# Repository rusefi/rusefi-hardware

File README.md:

# rusefi-hardware

open source repo just for rusEFI Hardware

See also https://github.com/rusefi/rusefi/tree/master/hardware

# Breakouts

Many adapters are available assembled at https://shop.rusefi.com

## Connect into wires

Connector on one side, screw terminals or pads for your own harness on the other

* [24 pin](breakout-boards/Breakout-24pin) generic 24 pin to three connectors
* [135 pin](breakout-boards/Breakout-135-subaru-single) Subaru single connector (3D models only)
* [154 pin](breakout-boards/Breakout_154pin_284617-1-Connector) Volkswagen Audi VAG 284617-1

More "connect into wires" breakouts (35 to 134 pin: Mazda, Chrysler NGC, Mitsubishi, Motronic, Ford EEC-IV, VAG, BMW) live in the main repo at https://github.com/rusefi/rusefi/tree/master/hardware

## Superseal adapters

Vehicle-specific adapters keep the original harness intact: stock ECU connector on one side, superseal into a rusEFI ECU on the other

* [24 pin superseal](breakout-boards/Breakout-24pin-superseal) same as 24 pin but going into superseal
* [112 pin](breakout-boards/adapter-board-me17-112-B-schematic.pdf) Bosch ME17 ([rev A](breakout-boards/adapter-board-me17-112-A-schematic.pdf))
* [121 pin](breakout-boards/Ferrari-Maserati-121-adapter-rev-a.pdf) Ferrari/Maserati F136 engine
* [154 pin](breakout-boards/Breakout_154_kia_pb) Hyundai/Kia 1.6 GDI PB ([pinout](https://rusefi.com/docs/pinouts/hellen/hellen-hyundai-pb-mt/))
* [198 pin](breakout-boards/Breakout-198-Mustang) Ford Mustang Coyote ([pinout](https://rusefi.com/docs/pinouts/hellen/coyote/))
* [Mazda Miata NC](breakout-boards/Breakout-mazda-nc-0.1.pdf) ([pinout](https://rusefi.com/docs/pinouts/miata-nc/))
* [Mitsubishi Lancer Evo X](breakout-boards/mitsubishi-lancer-evo-x-rev-a.pdf)
* [Mitsubishi Mirage](breakout-boards/mitsubishi-mirage-adapter-0.3.pdf)
* [Subaru 2011](subaru-2011-adapter-docs) ([vehicle pinout](https://rusefi.com/docs/pinouts/subaru-2011/), [adapter pinout](https://rusefi.com/docs/pinouts/subaru%20adapter/))
* [154 pin](breakout-boards/Passat-2.0-MED9.1-adapter.pdf) Volkswagen Passat 2.0 MED9.1 GDI

## Other

* [ZF 8HP](ZF8HP%20Transmission) transmission installation board, solders in place of the stock TCU

Vehicle connector pinouts (no board, just `connectors/*.yaml` for [interactive pinouts](https://rusefi.com/docs/pinouts/)):

* [BMW N52](BMW-N52-146) 146 pin ([pinout](https://rusefi.com/docs/pinouts/BMW-N52-146/))
* [BMW N54](BMW-N54-146) 146 pin ([pinout](https://rusefi.com/docs/pinouts/BMW-N54-146/))
* [Honda OBD1](honda-obd1) 64 pin + 76 pin ([pinout](https://rusefi.com/docs/pinouts/uaefi/honda-obd1/))
* [Toyota JZA80](Toyota-JZA80) Supra MK4 E9/E10
* [Toyota JZA90](Toyota-JZA90) Supra MK5
* [Jatco](jatco) transmission
* [Kawasaki](kawasaki) motorcycle

# Modules

* [A4988](A4988_stepper_motor_driver) stepper motor driver
* [L9779WD](L9779WD-breakout) ASIC breakout
* [MC33810](MC33810-breakout) ASIC breakout
* [TLE9104](tle9104-breakout) ASIC breakout
* [LM1949](Low-Z_LM1949) low impedance injector driver
* [IR2302](IR2302-testboard) test board
* [VR-Hall](VR-Hall) VR/Hall conditioner
* [NCV1124](VR_ncv1124_test_module) VR test module
* [frequency divider](frequency-divider)
* [quad IGBT](quad-igbt) and [superseal IGBT](superseal-igbt) ignition drivers
* [stm32 Brain board 48pin](mini48-stm32)
* [uaBrain GM E38](uaBrain-gm-e38) hw-uaBrain module carrier for GM E38 (draft)
* [GDI-4ch](GDI-4ch), [GDI-6ch](GDI-6ch), [GDI-STM](GDI-STM) direct injection drivers
* [lambda-x2](lambda-x2), [wideband-F103](wideband-F103) wideband controllers
* [CDI-test](CDI-test), [stim](stim), [digital-inputs](digital-inputs) test and QC boards

# Classic designs

Frankenso, Frankenstein and other legacy designs are in [classic-designs](classic-designs)

# Important note

Depends on libraries from https://github.com/rusefi/kicad-libraries

If you git clone be sure to also

`git submodule update --init`

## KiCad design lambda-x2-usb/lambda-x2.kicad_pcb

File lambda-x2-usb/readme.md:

# About

🟢 rev1 is known to work 🟢

pinout source https://github.com/rusefi/rusefi/tree/master/firmware/config/boards/lambda-x2

https://www.shop.rusefi.com/shop/p/dual-channel-wbo

Features:
* STM32F103 dual channel wideband AFR controller supporting Bosch LSU4.9 and LSU4.2 (LSU_ADV work in progress)
* CAN and analog output
* Bluetooth or USRT TunerStudio connectivity

Options (not icluded in default BOM)
* x2 EGT input using MAX31855KASA or MAX31856
* x2 auxilary analog input: 0..5V with pull-up or pull-down (configurable by soldering resistor). One can be used to source 5V to external sensor.
* x2 2 auxilary output 0..5V. Also can be used for slow PWM signal output.
* x2 open drain outputs

In development:
* MegaSquirt compatible pass-through connection over CAN http://www.msgpio.com/manuals/mshift/cpt.html (in progress)

See [interactive pinout](https://rusefi.com/docs/pinouts/lambda-x2/)

See [wire colors](https://github.com/rusefi/rusefi/wiki/WBO#naming-convention) for standart LSU wire collors and connectors pinouts.

Current stable [FW release](https://github.com/dron0gus/wideband/releases/tag/release_zero) use "dual-rev1" files

Firmware [sources](https://github.com/dron0gus/wideband) (based on https://github.com/mck1117/wideband).

See rusEFI forum: [F103 dual channel wideband controller + EGT + 2 x AUX In + 2 Aux out](https://rusefi.com/forum/viewtopic.php?f=4&t=2314)

See also https://github.com/rusefi/rusefi/wiki/WBO

# Known issues

## DFU mode/floating PB2

BOOT0 = 1, BOOT1 = 0 pattern is used to enter DFU bootloader on power/reset. BOOT0 is controled by jumper/button. BOOT1 (PB2) is used as bias current source for LSU4.9 and floating.

Use jumper wire to connect PB2 (through bias resistor) to GND: connect A2 pin of main connector with GND (J4 AUX connector pin 10)

## ESR measurement crosstalk between channels (rev0 and rev1)

HW has three different outputs for Nernst cell ESR measurement with different output resistance: 6.8K for LSU4.2, 22K for LSU4.9 and 47K for LSUADV. Idea was to allow the user to set the type of sensor from SW only.

Each ESR output is driven by one MCU GPIO. GPIOs for unused ESR measurement outputs are kept in Hi-Z (input) state and does not affect ESR measurement.

Same GPIO drivers ESR outputs for both channels. **This is the root cause of problem**

Problem: unused ESR output with GPIO in Hi-Z state connect Nernst cell outputs from left and right channel through two resistors. This causes crosstalk between channels and inaccurate ESR measurement. Wrong ESR measurement causes incorrect sensor temperature calculation. This can lead to inaccurate AFR measurement, overheating or underheating of the sensor.

Same issue for LSU4.9 bias resistors R22 and R70.

Solution:

Boards come with all ESR drive resistors populated. You have to remove unnecessary resistors.

If LSU4.2 sensor is used: remove R24, R25, R71, R72, R22, R70. Keep R41 and R73 - 6.8K

If LSU4.9 sensor is used: remove R25, R41, R72, R73. Keep R24 and R71 - 22K

If LSUADV sensor is used: remove R24, R41, R71, R73, R22, R70. Keep R25 and R72 - 47K

This will be (or not) solved in next revision of HW.

# Pinout

## Connectors pinout

[Main connector interactive Pinout](https://rusefi.com/docs/pinouts/lambda-x2/)

J4 is AUX connector available on PCB. SPI and I2C interfaces along with 3.3V and 5V are routed to this connector. Can be used to connect some small disply (SW not implemented yet)

J3 connector is for flashing and powering board on table. Also can be used for TunerStudion connection.

J1 and J2 are JTAG connectos.

## Uart pinout

J3 connector. Colors are default for cheap usb-to-uart converters based on CP2101 or FTDI232
Connect red wire if you want to power device from USB.
Default baud rate is 115200.

# Bluetooth

No extra steps needed to initialize JDY-33. Default device name is "RusEFI WBO x2" (or "RuseEFI WBO x2 BLE" for BT BLE)

Default baud rate is 115200.

# TunerStudio configuration

Baudrate is 115200
[.ini file](https://github.com/dron0gus/wideband/blob/master/firmware/ini/rusefi_wb_f1_dual.ini) for both UART and BT connection.

Both interfaces can be used simultaneously for data logging but not for settings change (from rev1).

Rev0 share same UART for both interfaces.

# Firmware Upload

Two ways to program using STM32CubeProgrammer

* recommended way: using UART connectivity. Power device up while shorting BOOT0 jumper to enter DFU mode (see "DFU mode/floating PB2" issue above)
* st-link if you have tc2030 spring-loaded cable.
* update over CAN or UART (J3) using OpenBLT (update over BT is in progress)

TL,DR: 9600 nothing connected on main connector

## Updating over UART using DFU mode

1. Disconnect main connector. If you are going to apply +12V power through main connector - make sure that nothing else is connected to WBO (LSU sensors, any load, etc). But I recommend flash using +5V from USB.
   
2. connect USB to uart connector to J3 connector: gnd, rx and tx.
Don't forget to cross Rx-`Tx (adapter's Tx goes to WBO's Rx, WBO's Tx goes to adapter's Rx).
If you going to power WBO from USB port - also attach 5V line. Do not connect +5 from USB adapter if you are going to use +12V supply through main connector.

### Linux way

3. Install stm32flash utility

`apt-get install stm32flash`

4. Press and hold BOOT0 button on the bottom of PCB. Or short BOOT0 PCB jumper if button is not populated on your board.

5. Apply power (while still holding BOOT0 button) to board

6. Run

`stm32flash /dev/ttyUSB0 -w wideband.hex`

### Windows way

3. Download and install STM32 Flash Loader Demonstrator. (Alternative tool is stm32flash - not covered in this instruction)

4. Figure out USB to serial serial port number: 

5. Start Flash Loader Demonstrator GUI application, select correct COM port. Optional: reduce timeout to 1 second:

6. Press and hold BOOT0 button on the bottom of PCB. Or short BOOT0 PCB jumper if button is not populated on your board.

7. Apply power (while holding BOOT0 button) to board and press Next in application. After app detects chip you should see something similar to:

8. Press next, select "Download to device", select wideband.bin file. Select "Jump to user application" and "Verify after download"

9. Press Next and wait for flash/verification ends.

## Updating using JTAG

DBD.

## Update using OpenBLT

OpenBLT https://www.feaser.com/openblt/doku.php

1. Restart device to OpenBLT mode using "Reset to OpenBLT" button under Controller -> ECU tools in TunerStudio.
   
2. Close TunerStudio to release serial port

3. Open BootCommander, select correct serial port, select wideband_update.srec file.

# Changelog

## rev 1
* Switch to 64 pin STM32/GD32
* Add 8MHz HSE oscillator (better clock stability for CAN over wide temperature range)
* Use DAC (instead of PWM) outputs for driving Ip
* Move BT to UART3/USART3, keep USART1 for bootloader/debug
* Drive BT's EN signal from MCU
* Fix RC filters on heater outputs for better voltage measurement
* Use separate ADC input for Vbat measurement
* Use ADC channels for AUX outputs monitoring/diagnostic
* Use PWM noise cancelation circuit on AUX analog outputs
* Removed useless/non-functional protection of Vm outputs
* Fix board outline to fit two types of enclosure ("plastic top" and "alloy brick")
* Add testpoints for TC2030 JTAG probe
* Add buttons for Reset and Boot0
* Add Cfg1 and jumpers
* Replace fuse holder with resettable 0.2A 33V fuse
* Two status LEDs for separate status indication for left and right channel
* Silkscreen labels around testpoints
* Silkscreen labels at uart connector on both sides of PCB
* Un_3x_sense formula is now 0.247 + 3.15 * (Un - Vm)
* Un_sense (not gained) is also routed to ADC input
* Protection from possible Ip current when MCU in reset/bootloader
* White "power on" LED replaced with green
* Main connector pinout added to top silkscreen
* AUX connector pinout added to top silkscreen

## rev 0

Seems to work with proper C10/C35 using https://github.com/rusefi/wideband/releases/tag/20230210-does-not-match-binaris

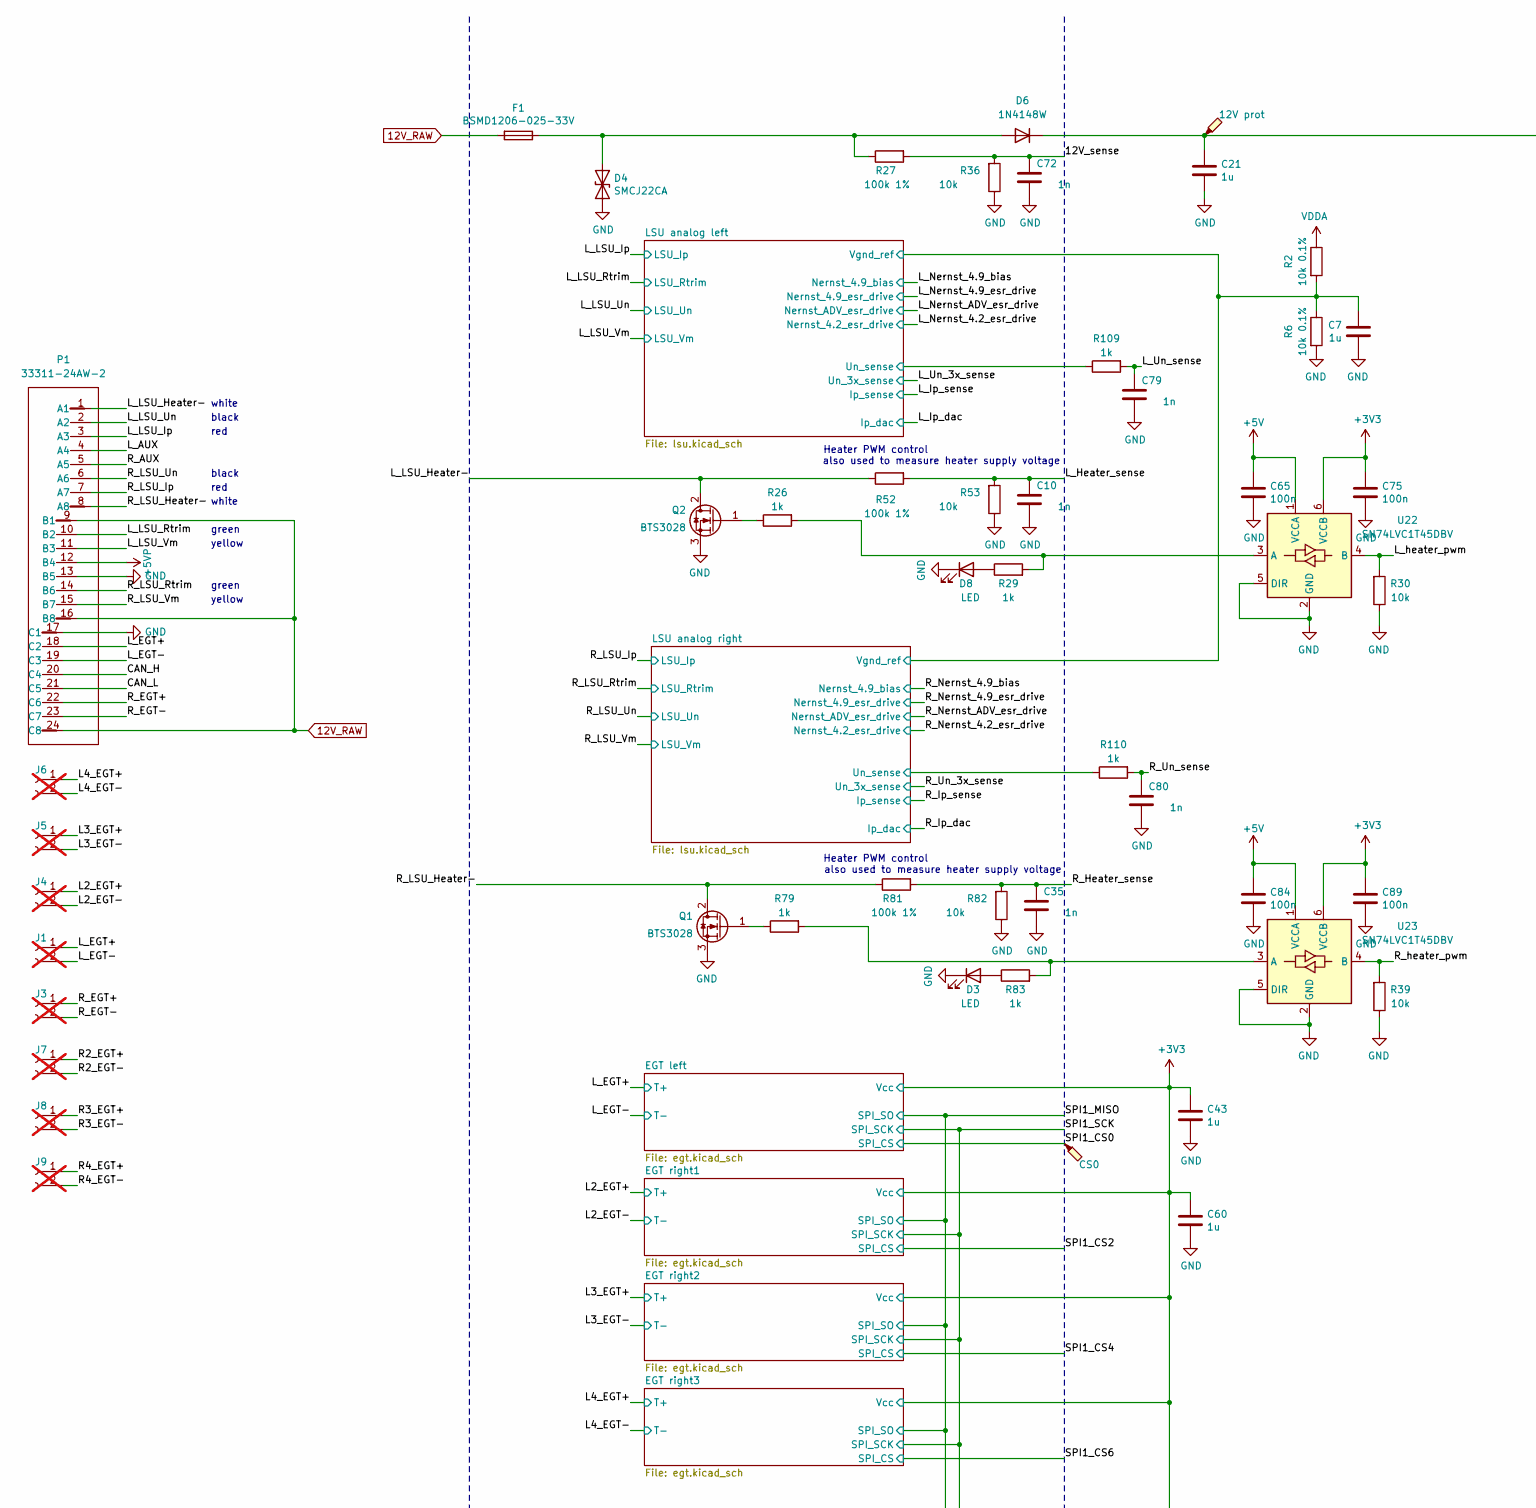
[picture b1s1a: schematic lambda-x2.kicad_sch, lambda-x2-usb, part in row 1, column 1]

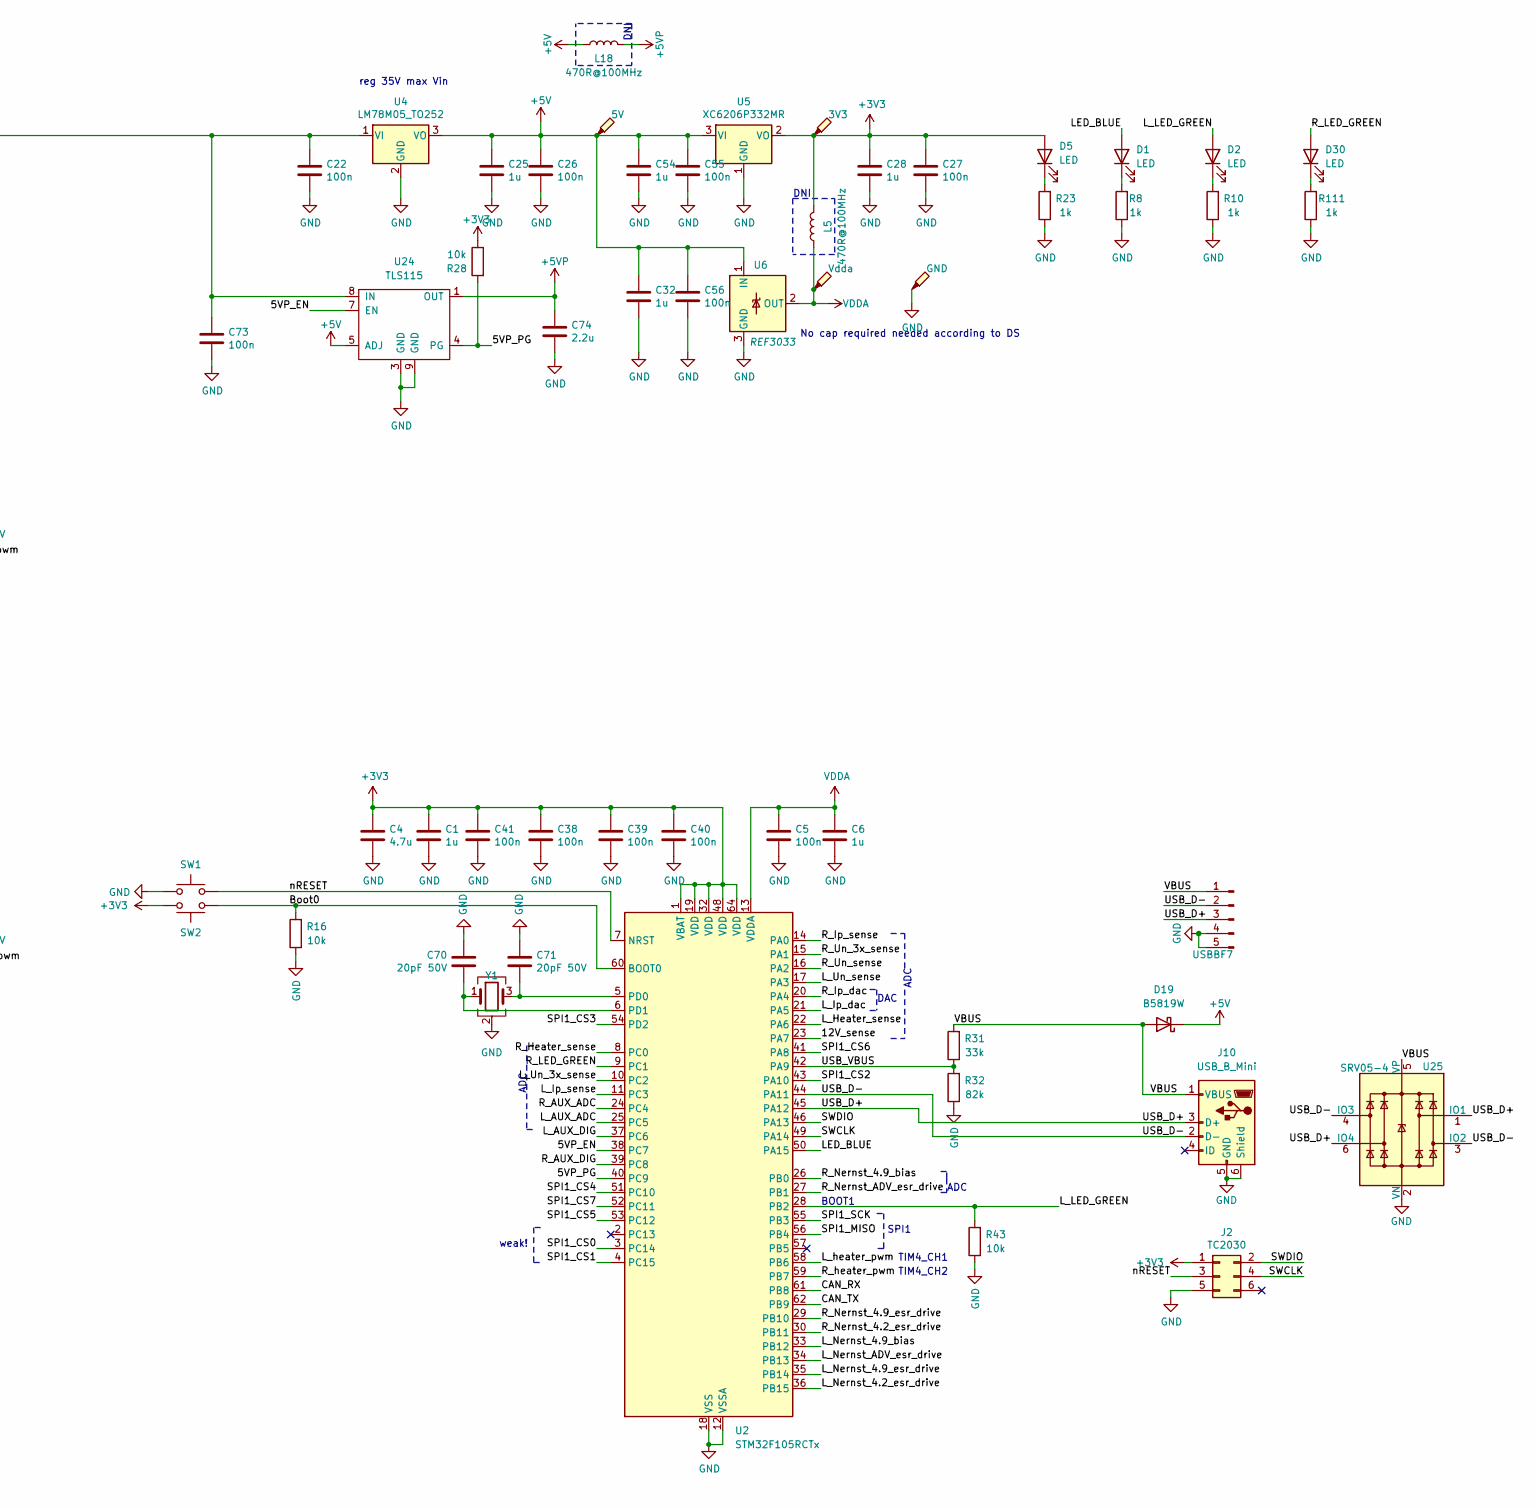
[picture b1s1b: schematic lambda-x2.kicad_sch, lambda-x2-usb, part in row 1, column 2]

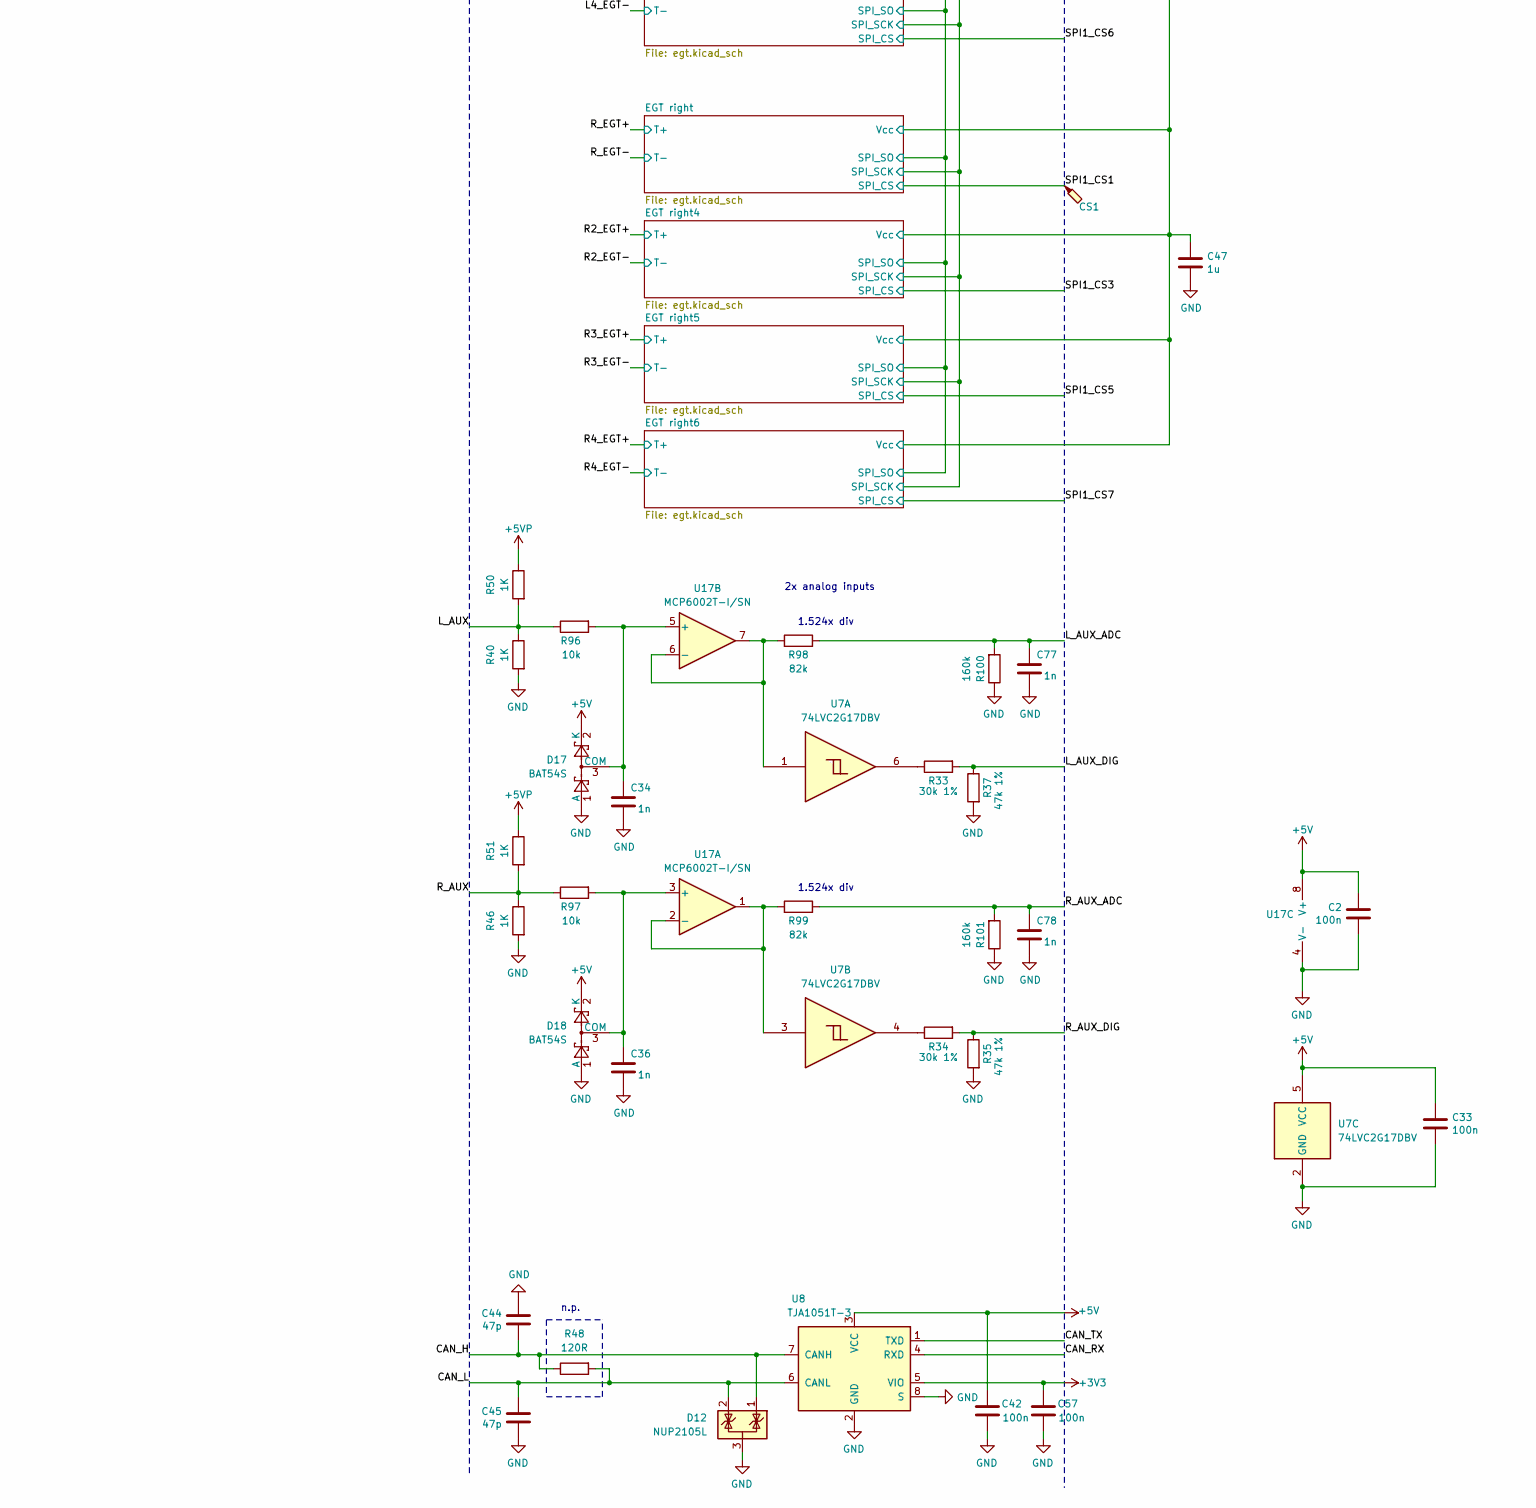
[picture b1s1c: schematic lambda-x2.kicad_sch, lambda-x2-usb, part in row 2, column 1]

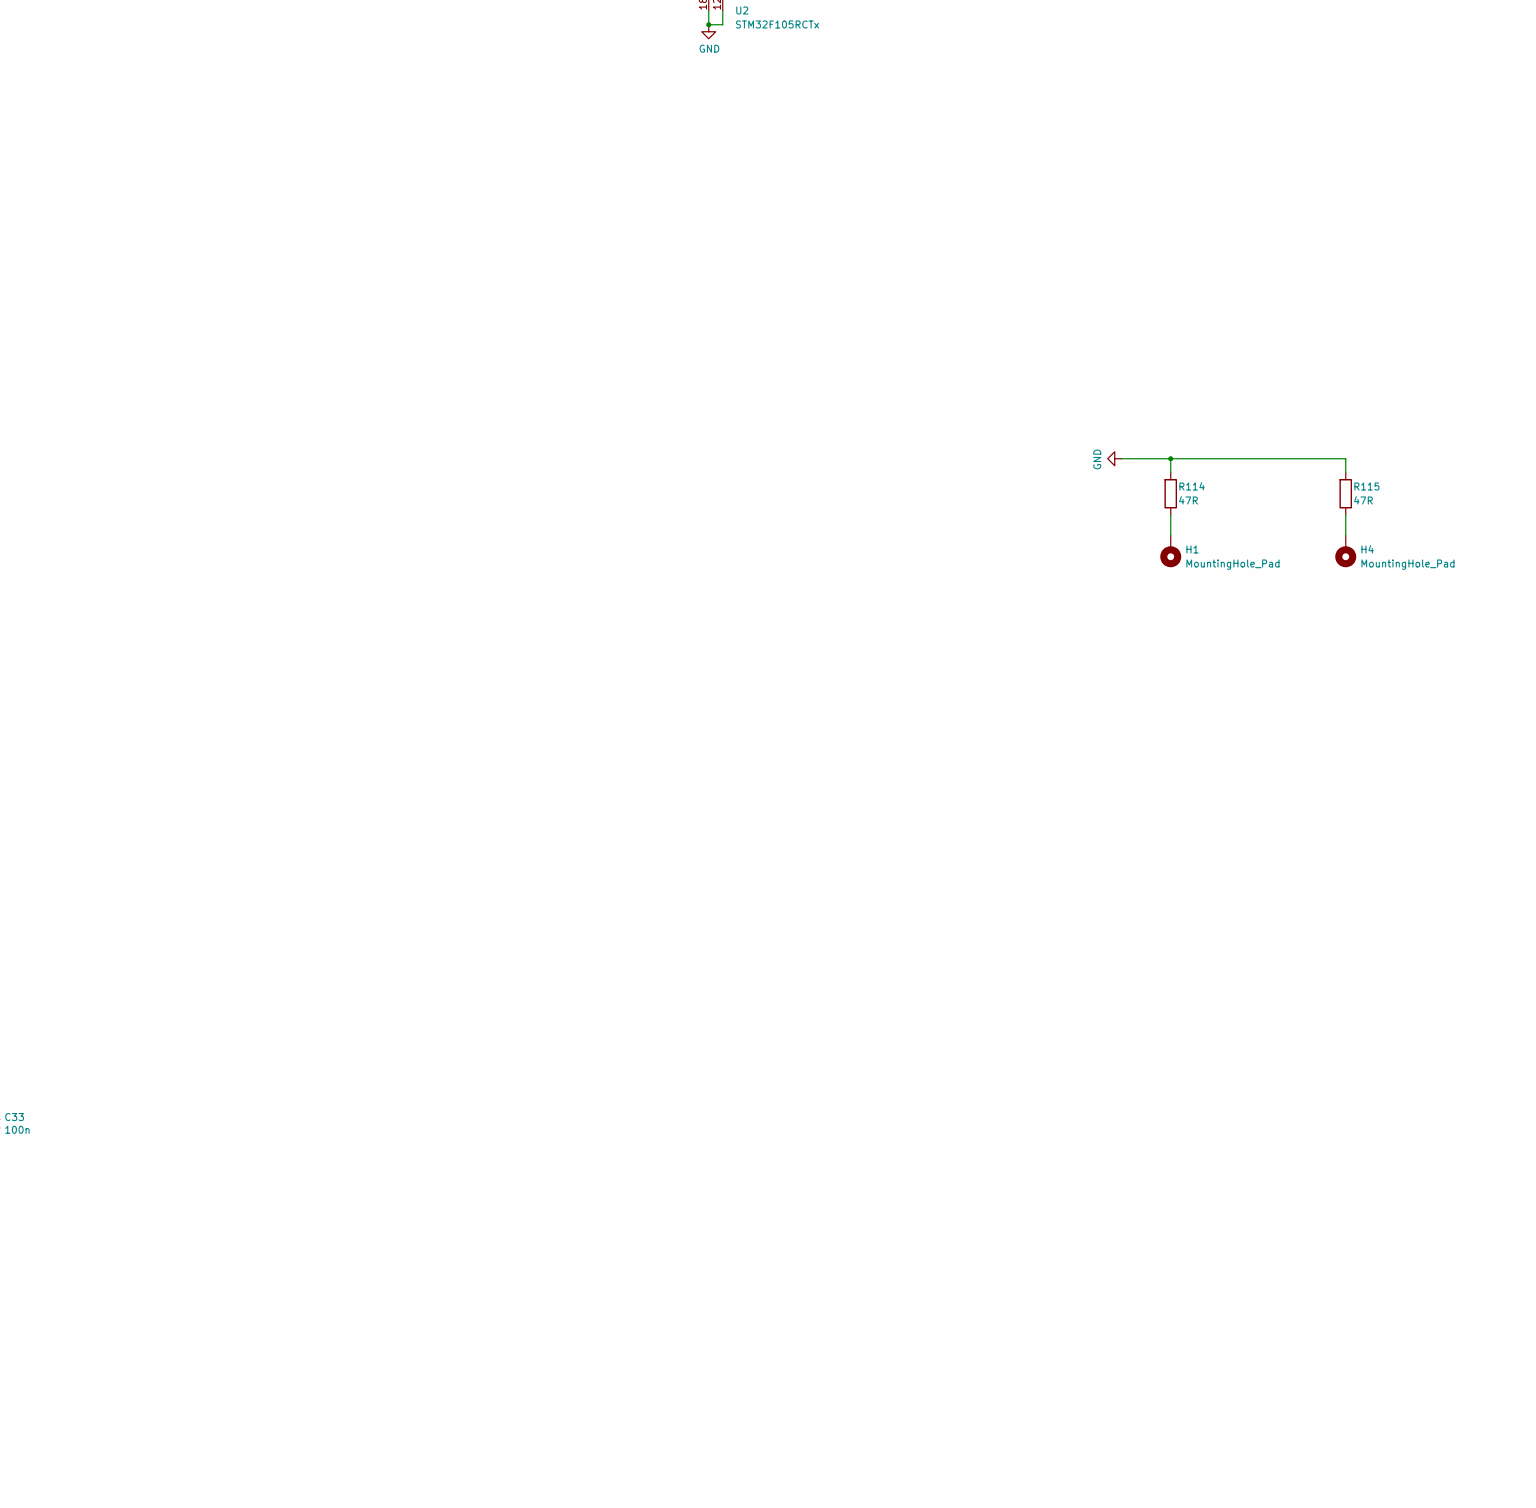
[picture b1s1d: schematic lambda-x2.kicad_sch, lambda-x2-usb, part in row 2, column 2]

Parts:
C1, C6, C7, C25, C28, C32, C43, C47, C54, C60: 1u; C_0402_1005Metric; LCSC C52923
C2, C5, C26, C27, C33, C38, C39, C40, C41, C42, C55, C56, C57, C65, C75, C84, C89: 100n; C_0402_1005Metric; LCSC C1525
C4: 4.7u; C_0402_1005Metric; LCSC C23733
C10, C34, C35, C36, C72, C77, C78, C79, C80: 1n; C_0402_1005Metric; LCSC C106205
C21: 1u; C_0603_1608Metric; LCSC C15849
C22, C73: 100n; C_0603_1608Metric; LCSC C14663
C44, C45: 47p; C_0402_1005Metric; LCSC C1567
C70, C71: 20pF 50V; C_0402_1005Metric; LCSC C107000
C74: 2.2u; C_0603_1608Metric; LCSC C23630
D1: LED; LED_0603_1608Metric; LCSC C497940
D2, D5, D30: LED; LED_0603_1608Metric; LCSC C965804
D3, D8: LED; LED_0603_1608Metric; LCSC C2286
D4: SMCJ22CA; D_SMC; LCSC C310038
D6: 1N4148W; D_SOD-123; LCSC C81598
D12: NUP2105L; SOT-23; LCSC C284104
D17, D18: BAT54S; SOT-23; LCSC C47546
D19: B5819W; D_SOD-123; LCSC C8598
F1: BSMD1206-025-33V; Fuse_1206_3216Metric; LCSC C2977524
H1, H4: MountingHole_Pad; MountingHole_2.5mm_Pad_Via
J1, J3, J4, J5, J7, J8, J9: Conn_01x02_Socket; PCC-SMP-V-one-leg; not fitted
J2: TC2030; Tag-Connect_TC2030-IDC-NL_2x03_P1.27mm_Vertical
J6: Conn_01x02_Socket; PCC-SMP-V; not fitted
J10: USB_B_Mini; USB-MINI-B-VERTICAL; LCSC C13453
J11: USBBF7; LCSC C17899327
L5, L18: 470R@100MHz; L_0603_1608Metric; LCSC C97853
P1: 33311-24AW-2; LCSC C5349068
Q1, Q2: BTS3028; TO-252-2; LCSC C112639
R2, R6: 10k 0.1%; R_0603_1608Metric; LCSC C309083
R8, R10, R23, R26, R29, R79, R83, R109, R110, R111: 1k; R_0402_1005Metric; LCSC C11702
R16, R28, R30, R36, R39, R43, R53, R82, R96, R97: 10k; R_0402_1005Metric; LCSC C25744
R27, R52, R81: 100k 1%; R_0603_1608Metric; LCSC C25803
R31: 33k; R_0402_1005Metric; LCSC C25779
R32: 82k; R_0402_1005Metric; LCSC C4142
R33, R34: 30k 1%; R_0603_1608Metric; LCSC C22984
R35, R37: 47k 1%; R_0603_1608Metric; LCSC C25819
R40, R46, R50, R51: 1K; R_0603_1608Metric; LCSC C21190
R48: 120R; R_1206_3216Metric; LCSC C176250
R98, R99: 82k; R_0402_1005Metric; LCSC C325373
R100, R101: 160k; R_0402_1005Metric; LCSC C409854
R114, R115: 47R; R_0603_1608Metric; LCSC C328363
SW1, SW2: SW_SPST_CK_RS282G05A3; LCSC C398054
TP7: 5V; TestPoint_Pad_D1.0mm
TP8: 3V3; TestPoint_Pad_D1.0mm
TP9: Vdda; TestPoint_Pad_D1.0mm
TP24: GND; TestPoint_Pad_D1.0mm
TP25: CS0; TestPoint_Pad_D1.0mm
TP26: CS1; TestPoint_Pad_D1.0mm
TP27: 12V prot; TestPoint_Pad_D1.0mm
U2: STM32F105RCTx; LQFP-64_10x10mm_P0.5mm; LCSC C8345
U4: LM78M05_TO252; TO-252-2; LCSC C58069
U5: XC6206P332MR; SOT-23-3; LCSC C5446
U6: REF3033; SOT-23; LCSC C36658
U7: 74LVC2G17DBV; SOT-23-6; LCSC C10429
U8: TJA1051T-3; SOIC-8_3.9x4.9mm_P1.27mm; LCSC C38695
U17: MCP6002T-I/SN; SOIC-8_3.9x4.9mm_P1.27mm; LCSC C7377
U22, U23: SN74LVC1T45DBV; SOT-23-6; LCSC C7843
U24: TLS115; PG-DSO-8-43; LCSC C3747428
U25: SRV05-4; SOT-23-6; LCSC C6454456
Y1: XXDCELNANF-8MHZ; Crystal_SMD_3225-4Pin_3.2x2.5mm; LCSC C367183

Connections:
12V_RAW: F1.2, P1.9 (B1), P1.16 (B8), P1.24 (C8)
+3V3: C1.1, C4.1, C27.1, C28.1, C38.1, C39.1, C40.1, C41.1, C43.1, C47.1, C57.1, C60.1, C75.1, C89.1, D5.2 (A), J2.1, L5.2, R28.1, SW2.2, TP8.1 (1_1), U2.1 (VBAT), U2.19 (VDD), U2.32 (VDD), U2.48 (VDD), U2.64 (VDD), U5.2 (VO), U8.5 (VIO), U22.6 (VCCB), U23.6 (VCCB); also elsewhere on the board
+5V: C2.1, C25.1, C26.1, C32.1, C33.1, C42.1, C54.1, C55.1, C56.1, C65.1, C84.1, D17.2 (K), D18.2 (K), D19.1 (K), L18.1, TP7.1 (1_1), U4.3 (VO), U5.3 (VI), U6.1 (IN), U7.5 (VCC), U8.3 (VCC), U17.8 (V+), U22.1 (VCCA), U23.1 (VCCA), U24.5 (ADJ)
+5VP: C74.1, L18.2, P1.12 (B4), R50.1, R51.1, U24.1 (OUT)
/5VP_EN: U2.38 (PC7), U24.7 (EN)
/5VP_PG: R28.2, U2.40 (PC9), U24.4 (PG)
/12V_sense: C72.1, R27.2, R36.2, U2.23 (PA7)
/Boot0: R16.2, SW2.1, U2.60 (BOOT0)
/CAN_H: C44.2, D12.1 (K), P1.20 (C4), R48.1, U8.7 (CANH)
/CAN_L: C45.1, D12.2 (K), P1.21 (C5), R48.2, U8.6 (CANL)
/CAN_RX: U2.61 (PB8), U8.4 (RXD)
/CAN_TX: U2.62 (PB9), U8.1 (TXD)
/L2_EGT+: J4.1; also elsewhere on the board
/L2_EGT-: J4.2; also elsewhere on the board
/L3_EGT+: J5.1; also elsewhere on the board
/L3_EGT-: J5.2; also elsewhere on the board
/L4_EGT+: J6.1; also elsewhere on the board
/L4_EGT-: J6.2; also elsewhere on the board
/LED_BLUE: D1.2 (A), U2.50 (PA15)
/LSU analog left/Un_sense: R109.1; also elsewhere on the board
/LSU analog left/Vgnd_ref: C7.1, R2.2, R6.1; also elsewhere on the board
/LSU analog right/Un_sense: R110.1; also elsewhere on the board
/L_AUX: P1.4 (A4), R40.1, R50.2, R96.1
/L_AUX_ADC: C77.1, R98.1, R100.2, U2.25 (PC5)
/L_AUX_DIG: R33.2, R37.1, U2.37 (PC6)
/L_EGT+: J1.1, P1.18 (C2); also elsewhere on the board
/L_EGT-: J1.2, P1.19 (C3); also elsewhere on the board
/L_Heater_sense: C10.1, R52.2, R53.2, U2.22 (PA6)
/L_Ip_dac: U2.21 (PA5); also elsewhere on the board
/L_Ip_sense: U2.11 (PC3); also elsewhere on the board
/L_LED_GREEN: D2.2 (A), R43.2, U2.28 (PB2)
/L_LSU_Heater-: P1.1 (A1), Q2.2 (D), R52.1
/L_LSU_Ip: P1.3 (A3); also elsewhere on the board
/L_LSU_Rtrim: P1.10 (B2); also elsewhere on the board
/L_LSU_Un: P1.2 (A2); also elsewhere on the board
/L_LSU_Vm: P1.11 (B3); also elsewhere on the board
/L_Nernst_4.2_esr_drive: U2.36 (PB15); also elsewhere on the board
/L_Nernst_4.9_bias: U2.33 (PB12); also elsewhere on the board
/L_Nernst_4.9_esr_drive: U2.35 (PB14); also elsewhere on the board
/L_Nernst_ADV_esr_drive: U2.34 (PB13); also elsewhere on the board
/L_Un_3x_sense: U2.10 (PC2); also elsewhere on the board
/L_Un_sense: C79.1, R109.2, U2.17 (PA3)
/L_heater_pwm: R30.2, U2.58 (PB6), U22.4 (B)
/R2_EGT+: J7.1; also elsewhere on the board
/R2_EGT-: J7.2; also elsewhere on the board
/R3_EGT+: J8.1; also elsewhere on the board
/R3_EGT-: J8.2; also elsewhere on the board
/R4_EGT+: J9.1; also elsewhere on the board
/R4_EGT-: J9.2; also elsewhere on the board
/R_AUX: P1.5 (A5), R46.1, R51.2, R97.1
/R_AUX_ADC: C78.1, R99.1, R101.2, U2.24 (PC4)
/R_AUX_DIG: R34.2, R35.1, U2.39 (PC8)
/R_EGT+: J3.1, P1.22 (C6); also elsewhere on the board
/R_EGT-: J3.2, P1.23 (C7); also elsewhere on the board
/R_Heater_sense: C35.1, R81.2, R82.2, U2.8 (PC0)
/R_Ip_dac: U2.20 (PA4); also elsewhere on the board
/R_Ip_sense: U2.14 (PA0); also elsewhere on the board
/R_LED_GREEN: D30.2 (A), U2.9 (PC1)
/R_LSU_Heater-: P1.8 (A8), Q1.2 (D), R81.1
/R_LSU_Ip: P1.7 (A7); also elsewhere on the board
/R_LSU_Rtrim: P1.14 (B6); also elsewhere on the board
/R_LSU_Un: P1.6 (A6); also elsewhere on the board
/R_LSU_Vm: P1.15 (B7); also elsewhere on the board
/R_Nernst_4.2_esr_drive: U2.30 (PB11); also elsewhere on the board
/R_Nernst_4.9_bias: U2.26 (PB0); also elsewhere on the board
/R_Nernst_4.9_esr_drive: U2.29 (PB10); also elsewhere on the board
/R_Nernst_ADV_esr_drive: U2.27 (PB1); also elsewhere on the board
/R_Un_3x_sense: U2.15 (PA1); also elsewhere on the board
/R_Un_sense: C80.1, R110.2, U2.16 (PA2)
/R_heater_pwm: R39.2, U2.59 (PB7), U23.4 (B)
/SPI1_CS0: TP25.1 (1_1), U2.3 (PC14); also elsewhere on the board
/SPI1_CS1: TP26.1 (1_1), U2.4 (PC15); also elsewhere on the board
/SPI1_CS2: U2.43 (PA10); also elsewhere on the board
/SPI1_CS3: U2.54 (PD2); also elsewhere on the board
/SPI1_CS4: U2.51 (PC10); also elsewhere on the board
/SPI1_CS5: U2.53 (PC12); also elsewhere on the board
/SPI1_CS6: U2.41 (PA8); also elsewhere on the board
/SPI1_CS7: U2.52 (PC11); also elsewhere on the board
/SPI1_MISO: U2.56 (PB4); also elsewhere on the board
/SPI1_SCK: U2.55 (PB3); also elsewhere on the board
/SWCLK: J2.4, U2.49 (PA14)
/SWDIO: J2.2, U2.46 (PA13)
/USB_D+: J10.3 (D+), J11.3, U2.45 (PA12), U25.1 (IO1), U25.6 (IO4)
/USB_D-: J10.2 (D-), J11.2, U2.44 (PA11), U25.3 (IO2), U25.4 (IO3)
/USB_VBUS: R31.1, R32.2, U2.42 (PA9)
/VBUS: D19.2 (A), J10.1 (VBUS), J11.1, R31.2, U25.5 (VP)
/nRESET: J2.3, SW1.2, U2.7 (NRST)
GND: C1.2, C2.2, C4.2, C5.2, C6.2, C7.2, C10.2, C21.2, C22.2, C25.2, C26.2, C27.2, C28.2, C32.2, C33.2, C34.2, C35.2, C36.2, C38.2, C39.2, C40.2, C41.2, C42.2, C43.2, C44.1, C45.2, C47.2, C54.2, C55.2, C56.2, C57.2, C60.2, C65.2, C70.1, C71.1, C72.2, C73.2, C74.2, C75.2, C77.2, C78.2, C79.2, C80.2, C84.2, C89.2, D3.1 (K), D4.2 (A2), D8.1 (K), D12.3 (A), D17.1 (A), D18.1 (A), J2.5, J10.5 (GND), J10.6 (Shield), J11.4, J11.5, P1.13 (B5), P1.17 (C1), Q1.3 (S), Q2.3 (S), R6.2, R8.1, R10.1, R16.1, R23.1, R30.1, R32.1, R35.2, R36.1, R37.2, R39.1, R40.2, R43.1, R46.2, R53.1, R82.1, R100.1, R101.1, R111.1, R114.2, R115.2, SW1.1, TP24.1 (1_1), U2.12 (VSSA), U2.18 (VSS), U2.31 (VSS), U2.47 (VSS), U2.63 (VSS), U4.2 (GND), U5.1 (GND), U6.3 (GND), U7.2 (GND), U8.2 (GND), U8.8 (S), U17.4 (V-), U22.2 (GND), U22.5 (DIR), U23.2 (GND), U23.5 (DIR), U24.3 (GND), U24.9 (GND), U25.2 (VN), Y1.2 (G), Y1.4 (G); also elsewhere on the board
unnamed: D1.1 (K), R8.2
unnamed: D2.1 (K), R10.2
unnamed: D3.2 (A), R83.1
unnamed: D4.1 (A1), D6.2 (A), F1.1, R27.1
unnamed: D5.1 (K), R23.2
unnamed: C21.1, C22.1, C73.1, D6.1 (K), TP27.1 (1_1), U4.1 (VI), U24.8 (IN)
unnamed: D8.2 (A), R29.1
unnamed: C34.1, D17.3 (COM), R96.2, U17.5 (+)
unnamed: C36.1, D18.3 (COM), R97.2, U17.3 (+)
unnamed: D30.1 (K), R111.2
unnamed: H1.1 (1_1), R114.1
unnamed: H4.1 (1_1), R115.1
unnamed: Q1.1 (G), R79.1
unnamed: Q2.1 (G), R26.1
unnamed: R33.1, U7.6
unnamed: R34.1, U7.4
unnamed: C71.2, U2.5 (PD0), Y1.3
unnamed: C70.2, U2.6 (PD1), Y1.1
unnamed: R99.2, U7.3, U17.1, U17.2 (-)
unnamed: R98.2, U7.1, U17.6 (-), U17.7
unnamed: R26.2, R29.2, U22.3 (A)
unnamed: R79.2, R83.2, U23.3 (A)
VDDA: C5.1, C6.1, L5.1, R2.1, TP9.1 (1_1), U2.13 (VDDA), U6.2 (OUT); also elsewhere on the board

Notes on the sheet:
yellow
No cap required needed according to DS
red
weak!
reg 35V max Vin
SPI1
Heater PWM control
DNI
white
DAC
black
green
n.p.
ADC
TIM4_CH2
1.524x div
BOOT1
also used to measure heater supply voltage
2x analog inputs
TIM4_CH1

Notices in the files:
digital-inputs/firmware/board/board.h:
ChibiOS - Copyright (C) 2006..2018 Giovanni Di Sirio
Licensed under the Apache License, Version 2.0 (the "License");
